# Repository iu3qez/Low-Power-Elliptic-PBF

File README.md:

Ellic Low Power Pand Pass Filter. Up to max 200 Watt.

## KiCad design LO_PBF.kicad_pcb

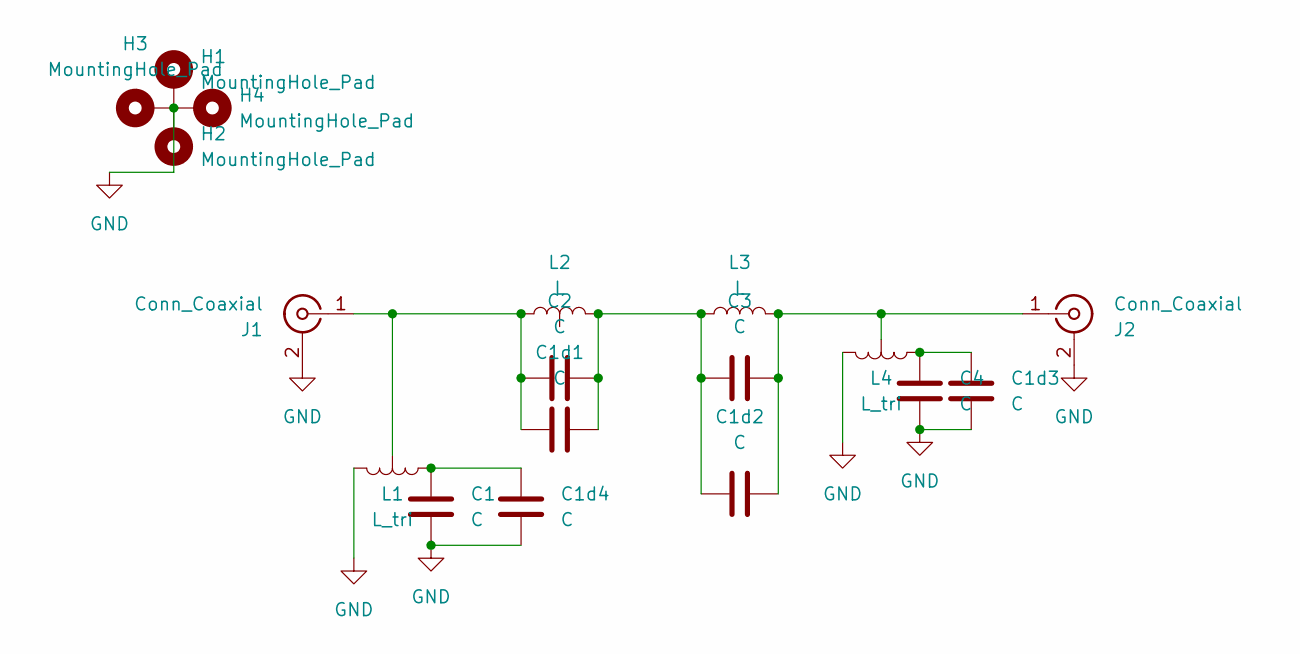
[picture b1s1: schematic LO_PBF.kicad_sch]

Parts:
C1, C2, C3, C4: C; condensatore_VA6AM_5
C1d1, C1d2, C1d3, C1d4: C; C_1812_multiplo
H1, H2, H3, H4: MountingHole_Pad; MountingHole_3.2mm_M3_Pad
J1, J2: Conn_Coaxial; coax_solder
L1, L4: L_tri; va6am_induttore_3_pin_split
L2, L3: L; va6am_induttore

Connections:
GND: C1.2, C1d3.1, C1d4.2, C4.2, H1.1, H2.1, H3.1, H4.1, J1.2 (Ext), J2.2 (Ext), L1.3, L4.3
unnamed: C1.1, C1d4.1, L1.1
unnamed: C1d1.2, C1d2.1, C2.1, C3.2, L2.2, L3.1
unnamed: C1d3.2, C4.1, L4.1
unnamed: C1d1.1, C2.2, J1.1 (In), L1.2, L2.1
unnamed: C1d2.2, C3.1, J2.1 (In), L3.2, L4.2

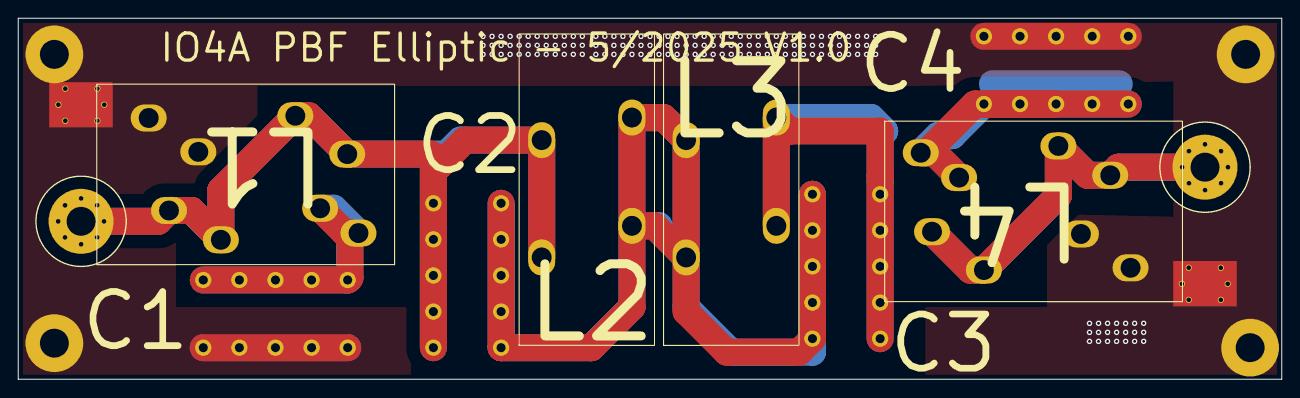
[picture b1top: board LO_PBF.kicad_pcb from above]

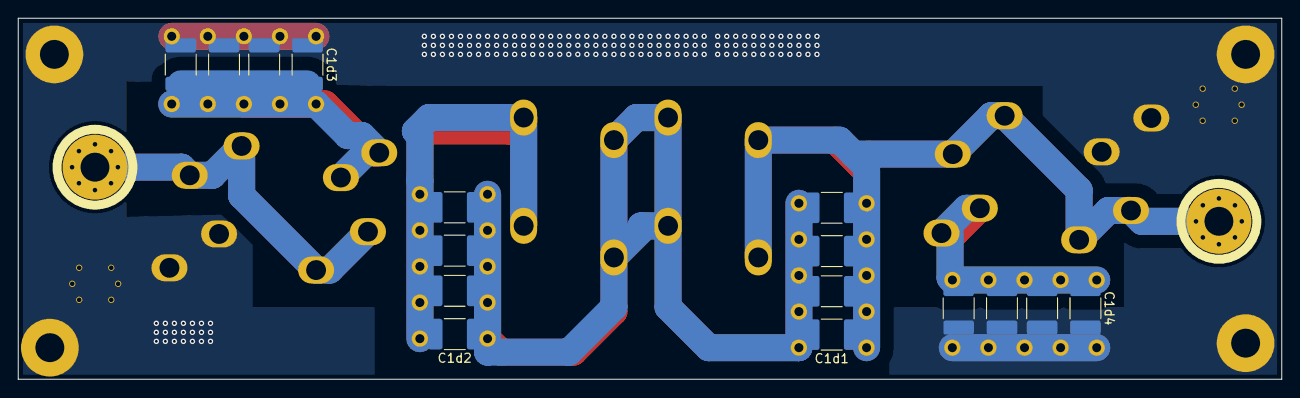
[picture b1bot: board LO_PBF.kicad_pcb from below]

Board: 2 copper layers, 140.0 x 40.0 mm, 18 parts (4 on the bottom side), 6 nets.

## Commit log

2025-08-05 like ordered to JLCPCB
